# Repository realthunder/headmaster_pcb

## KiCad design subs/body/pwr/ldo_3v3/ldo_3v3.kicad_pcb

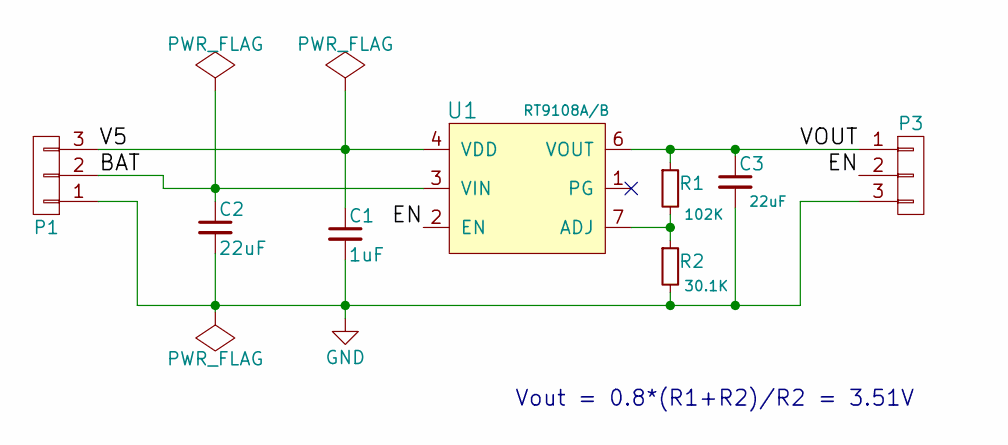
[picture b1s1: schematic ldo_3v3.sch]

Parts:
C1: 1uF; C_0402
C2, C3: 22uF; C_0805
P1, P3: CONN_01X01; Pin_Header_Straight_1x03
R1: 102K; R_0402
R2: 30.1K; R_0402
U1: RT9108A/B; SOIC-8-1EP_3.9x4.9mm_Pitch1.27mm

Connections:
/BAT: C2.1, P1.2, U1.3 (VIN)
/EN: P3.2, U1.2 (EN)
/V5: C1.1, P1.3, U1.4 (VDD)
/VOUT: C3.1, P3.1, R1.1, U1.6 (VOUT)
GND: C1.2, C2.2, C3.2, P1.1, P3.3, R2.2, U1.8 (GND), U1.9 (GND)
unnamed: R1.2, R2.1, U1.7 (ADJ)

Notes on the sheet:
Vout = 0.8*(R1+R2)/R2 = 3.51V

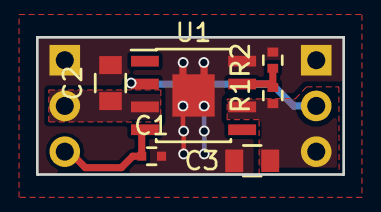
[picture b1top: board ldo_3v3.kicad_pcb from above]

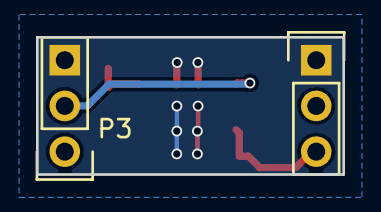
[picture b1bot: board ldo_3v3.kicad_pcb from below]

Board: 2 copper layers, 17.0 x 7.6 mm, 8 parts (2 on the bottom side), 6 nets.

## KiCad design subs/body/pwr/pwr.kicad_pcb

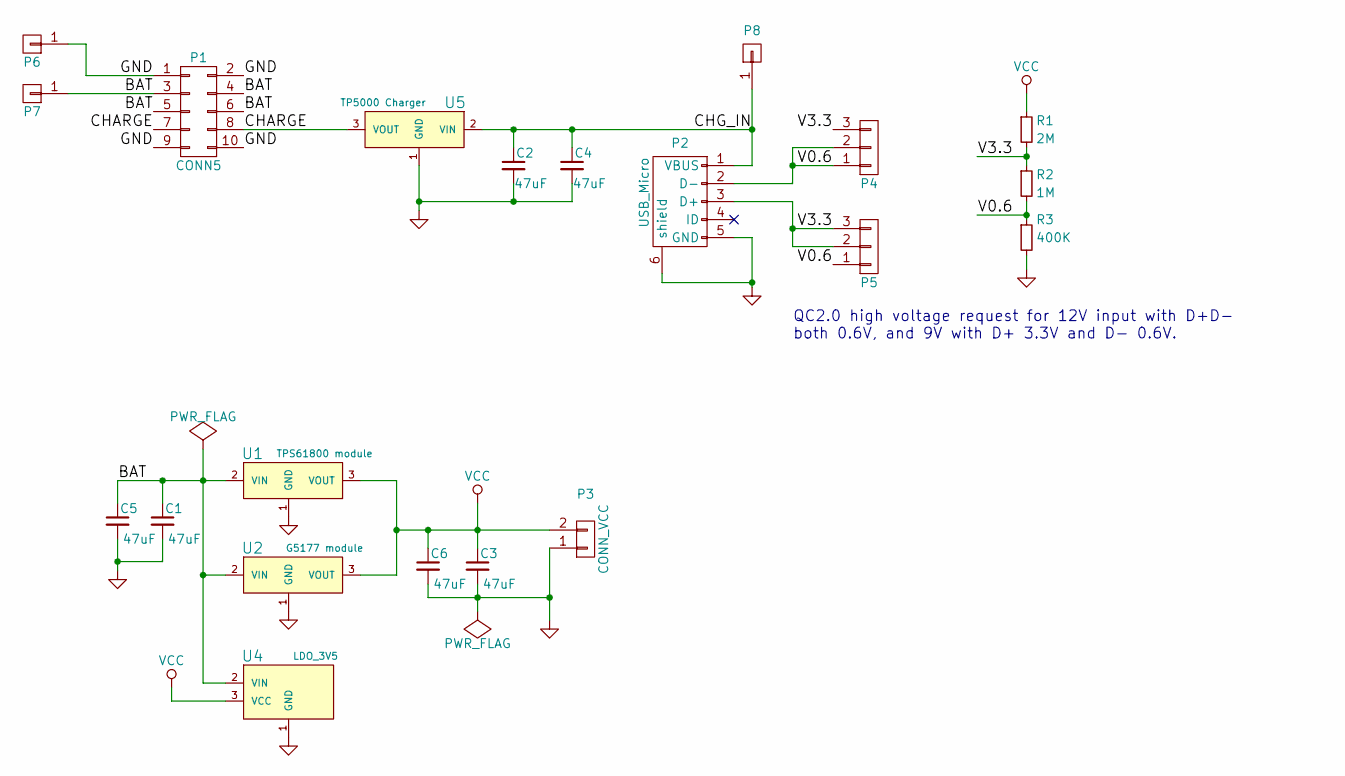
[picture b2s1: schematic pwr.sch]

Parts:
C1, C2, C3, C4, C5, C6: 47uF; C_1206
P1: CONN5; Socket_Strip_Straight_2x05
P2: USB_Micro; USB_Micro-B
P3: CONN_VCC; Socket_Strip_Straight_1x02
P4, P5: CONN_01X03; Pin_Header_Straight_1x03_Pitch1.27mm
P6, P7, P8: CONN_01X01; Pin_Header_Straight_1x01
R1: 2M; R_0402
R2: 1M; R_0402
R3: 400K; R_0402
U1: TPS61800 module; DCDC_Conv_TPS61800-Boost
U2: G5177 module; DCDC_Conv_G5177-Boost
U4: LDO_3V5; LDO_RT9018
U5: TP5000 Charger; DCDC_Charger-TP5000-Bucket

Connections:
/BAT: C1.1, C5.1, P1.3, P1.4, P1.5, P1.6, P7.1, U1.2 (VIN), U2.2 (VIN), U4.2 (VIN)
/CHARGE: P1.7, P1.8, U5.3 (VOUT)
/CHG_IN: C2.1, C4.1, P2.1 (VBUS), P8.1, U5.2 (VIN)
/V0.6: P2.2 (D-), P4.1, P4.2, P5.1, R2.2, R3.1
/V3.3: P2.3 (D+), P4.3, P5.2, P5.3, R1.2, R2.1
GND: C1.2, C2.2, C3.2, C4.2, C5.2, C6.2, P1.1, P1.2, P1.9, P1.10, P2.5 (GND), P2.6 (shield), P3.1, P6.1, R3.2, U1.1 (GND), U2.1 (GND), U4.1 (GND), U5.1 (GND)
VCC: C3.1, C6.1, P3.2, R1.1, U1.3 (VOUT), U2.3 (VOUT), U4.3 (VCC)

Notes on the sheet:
QC2.0 high voltage request for 12V input with D+D- both 0.6V, and 9V with D+ 3.3V and D- 0.6V.

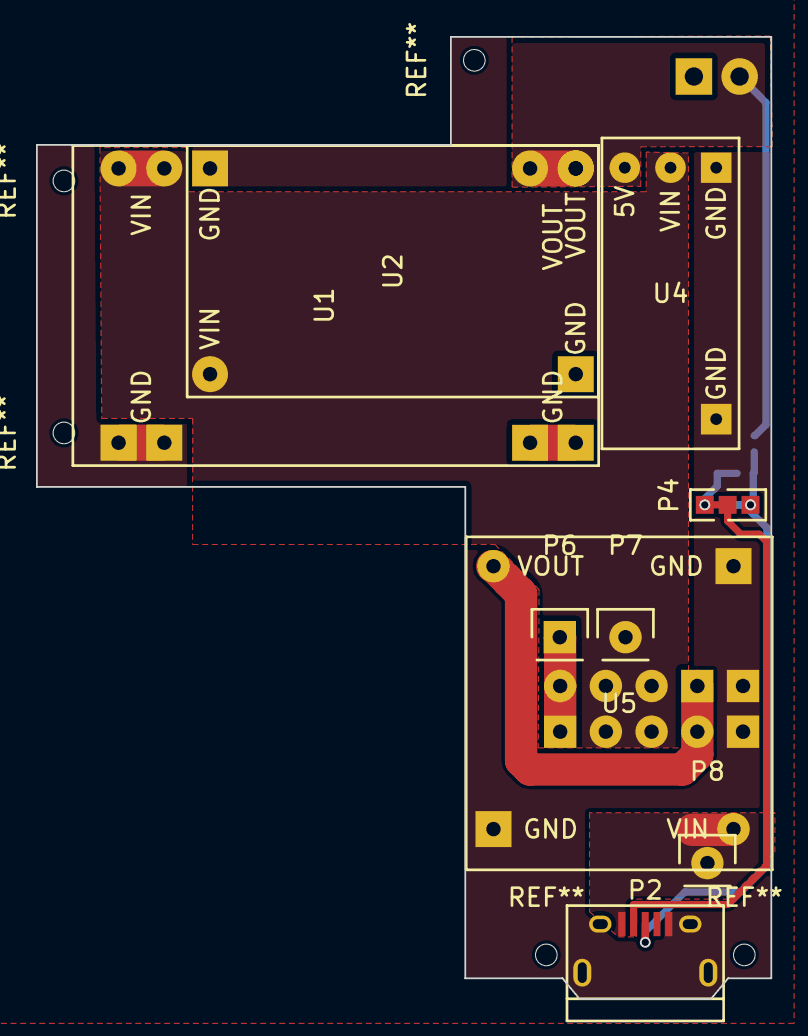
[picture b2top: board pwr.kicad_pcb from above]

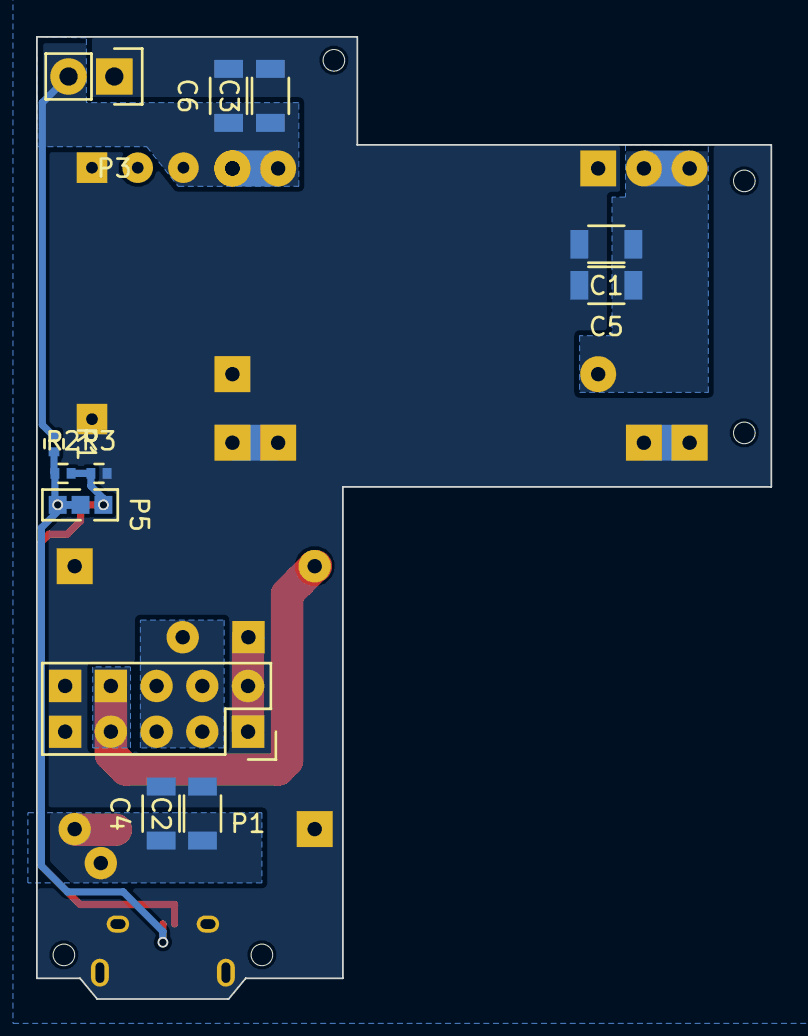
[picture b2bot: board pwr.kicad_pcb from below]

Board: 2 copper layers, 40.8 x 53.4 mm, 21 parts (12 on the bottom side), 7 nets.

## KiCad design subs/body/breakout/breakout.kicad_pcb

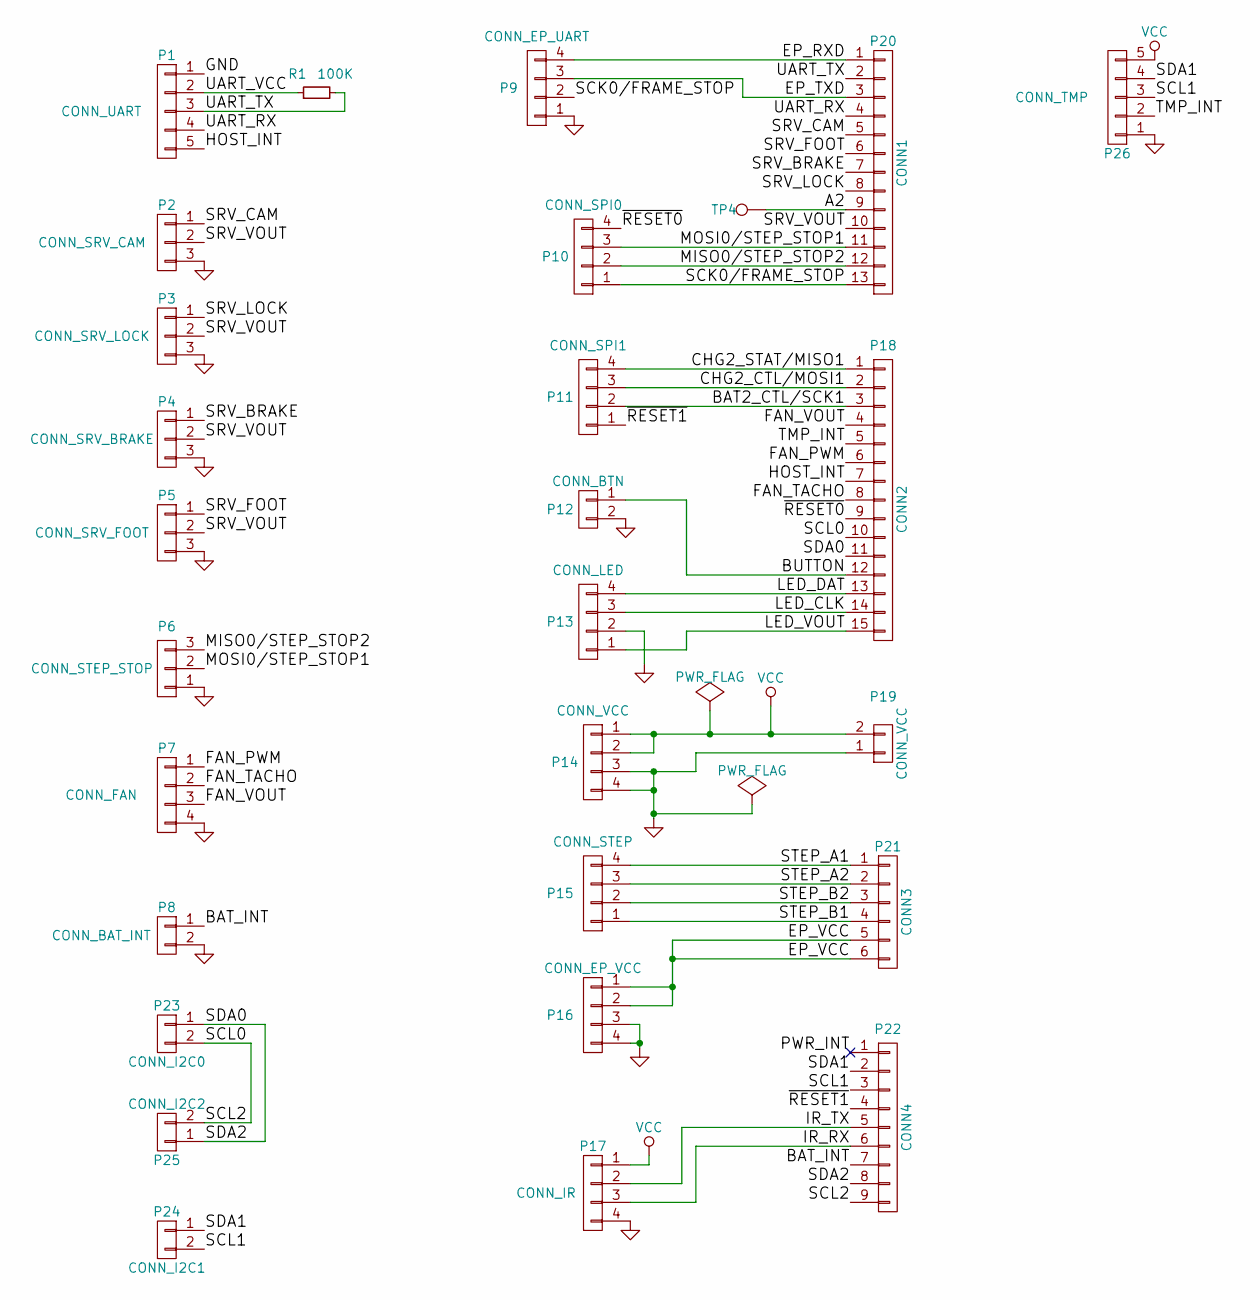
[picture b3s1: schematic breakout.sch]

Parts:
P1: CONN_UART; Molex_PicoBlade_53047-0510_DoubleSide
P2: CONN_SRV_CAM; Molex_PicoBlade_53047-0310_DoubleSide
P3: CONN_SRV_LOCK; Molex_PicoBlade_53047-0310_DoubleSide
P4: CONN_SRV_BRAKE; Molex_PicoBlade_53047-0310_DoubleSide
P5: CONN_SRV_FOOT; Molex_PicoBlade_53047-0310_DoubleSide
P6: CONN_STEP_STOP; Molex_PicoBlade_53047-0310_DoubleSide
P7: CONN_FAN; Molex_PicoBlade_53047-0410_DoubleSide
P8: CONN_BAT_INT; Molex_PicoBlade_53047-0210_DoubleSide
P9: CONN_EP_UART; Molex_PicoBlade_53047-0410_DoubleSide
P10: CONN_SPI0; Pin_Header_Straight_1x04_Pitch1.27mm
P11: CONN_SPI1; Pin_Header_Straight_1x04_Pitch1.27mm
P12: CONN_BTN; Molex_PicoBlade_53047-0210_DoubleSide
P13: CONN_LED; Molex_PicoBlade_53047-0410_DoubleSide
P14: CONN_VCC; Molex_PicoBlade_53047-0410_DoubleSide
P15: CONN_STEP; Molex_PicoBlade_53047-0410_DoubleSide
P16: CONN_EP_VCC; Molex_PicoBlade_53047-0410_DoubleSide
P17: CONN_IR; Molex_PicoBlade_53047-0410_DoubleSide
P18: CONN2; Socket_Strip_Straight_1x15_Pitch1.27mm
P19: CONN_VCC; Socket_Strip_Straight_1x02
P20: CONN1; Socket_Strip_Straight_1x13_Pitch1.27mm
P21: CONN3; Socket_Strip_Straight_1x06_Pitch1.27mm
P22: CONN4; Socket_Strip_Straight_1x09_Pitch1.27mm
P23: CONN_I2C0; Pin_Header_Straight_1x02_Pitch1.27mm
P24: CONN_I2C1; Molex_PicoBlade_53047-0210_DoubleSide
P25: CONN_I2C2; Pin_Header_Straight_1x02_Pitch1.27mm
P26: CONN_TMP; Molex_PicoBlade_53047-0510_DoubleSide
R1: 100K; R_0402
TP4: TEST_1P; Pin_Header_Straight_1x01_Pitch1.27mm

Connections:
/A2: P20.9, TP4.1
/BAT2_CTL/SCK1: P11.2, P18.3
/BAT_INT: P8.1, P22.7
/BUTTON: P12.1, P18.12
/CHG2_CTL/MOSI1: P11.3, P18.2
/CHG2_STAT/MISO1: P11.4, P18.1
/EP_RXD: P9.4, P20.1
/EP_TXD: P9.3, P20.3
/EP_VCC: P16.1, P16.2, P21.5, P21.6
/FAN_PWM: P7.1, P18.6
/FAN_TACHO: P7.2, P18.8
/FAN_VOUT: P7.3, P18.4
/HOST_INT: P1.5, P18.7
/IR_RX: P17.3, P22.6
/IR_TX: P17.2, P22.5
/LED_CLK: P13.3, P18.14
/LED_DAT: P13.4, P18.13
/LED_VOUT: P13.1, P18.15
/MISO0/STEP_STOP2: P6.3, P10.2, P20.12
/MOSI0/STEP_STOP1: P6.2, P10.3, P20.11
/SCK0/FRAME_STOP: P9.2, P10.1, P20.13
/SCL0: P18.10, P22.9, P23.2, P25.2
/SCL1: P22.3, P24.2, P26.3
/SDA0: P18.11, P22.8, P23.1, P25.1
/SDA1: P22.2, P24.1, P26.4
/SRV_BRAKE: P4.1, P20.7
/SRV_CAM: P2.1, P20.5
/SRV_FOOT: P5.1, P20.6
/SRV_LOCK: P3.1, P20.8
/SRV_VOUT: P2.2, P3.2, P4.2, P5.2, P20.10
/STEP_A1: P15.4, P21.1
/STEP_A2: P15.3, P21.2
/STEP_B1: P15.1, P21.4
/STEP_B2: P15.2, P21.3
/TMP_INT: P18.5, P26.2
/UART_RX: P1.4, P20.4
/UART_TX: P1.3, P20.2, R1.2
/UART_VCC: P1.2, R1.1
/~RESET0: P10.4, P18.9
/~RESET1: P11.1, P22.4
GND: P1.1, P2.3, P3.3, P4.3, P5.3, P6.1, P7.4, P8.2, P9.1, P12.2, P13.2, P14.3, P14.4, P16.3, P16.4, P17.4, P19.1, P26.1
VCC: P14.1, P14.2, P17.1, P19.2, P26.5

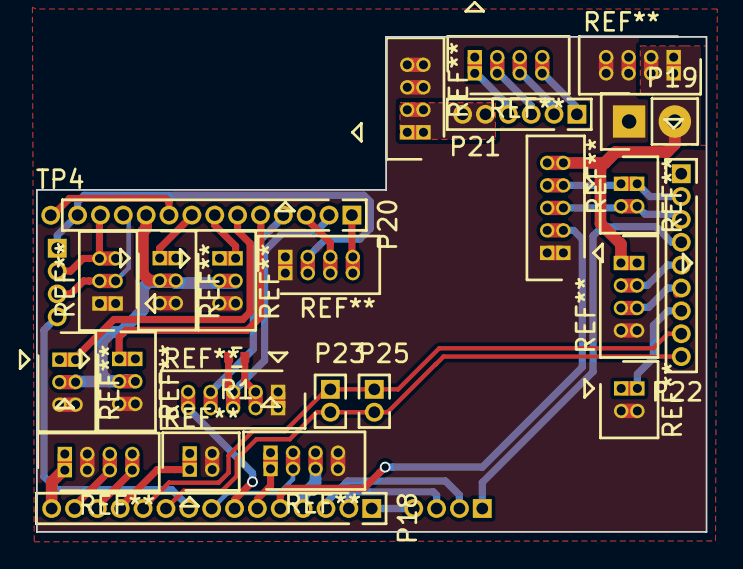
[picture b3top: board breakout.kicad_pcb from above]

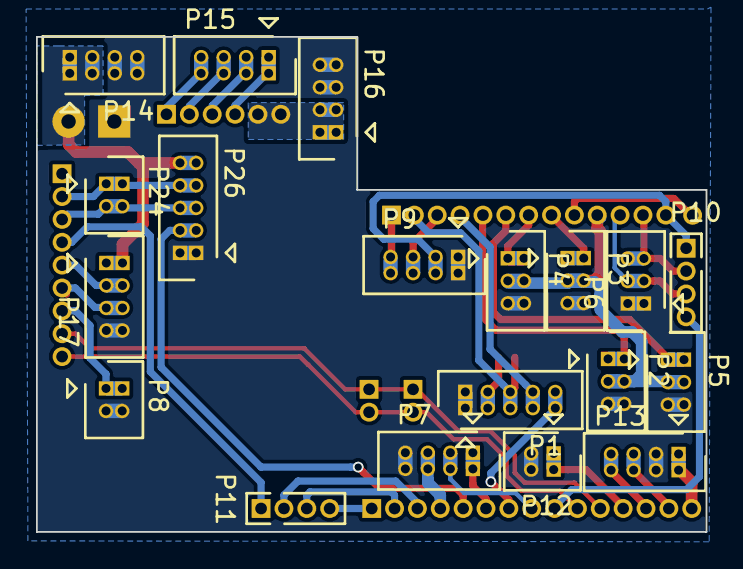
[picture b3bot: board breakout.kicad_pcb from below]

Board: 2 copper layers, 37.2 x 27.5 mm, 28 parts (19 on the bottom side), 42 nets.

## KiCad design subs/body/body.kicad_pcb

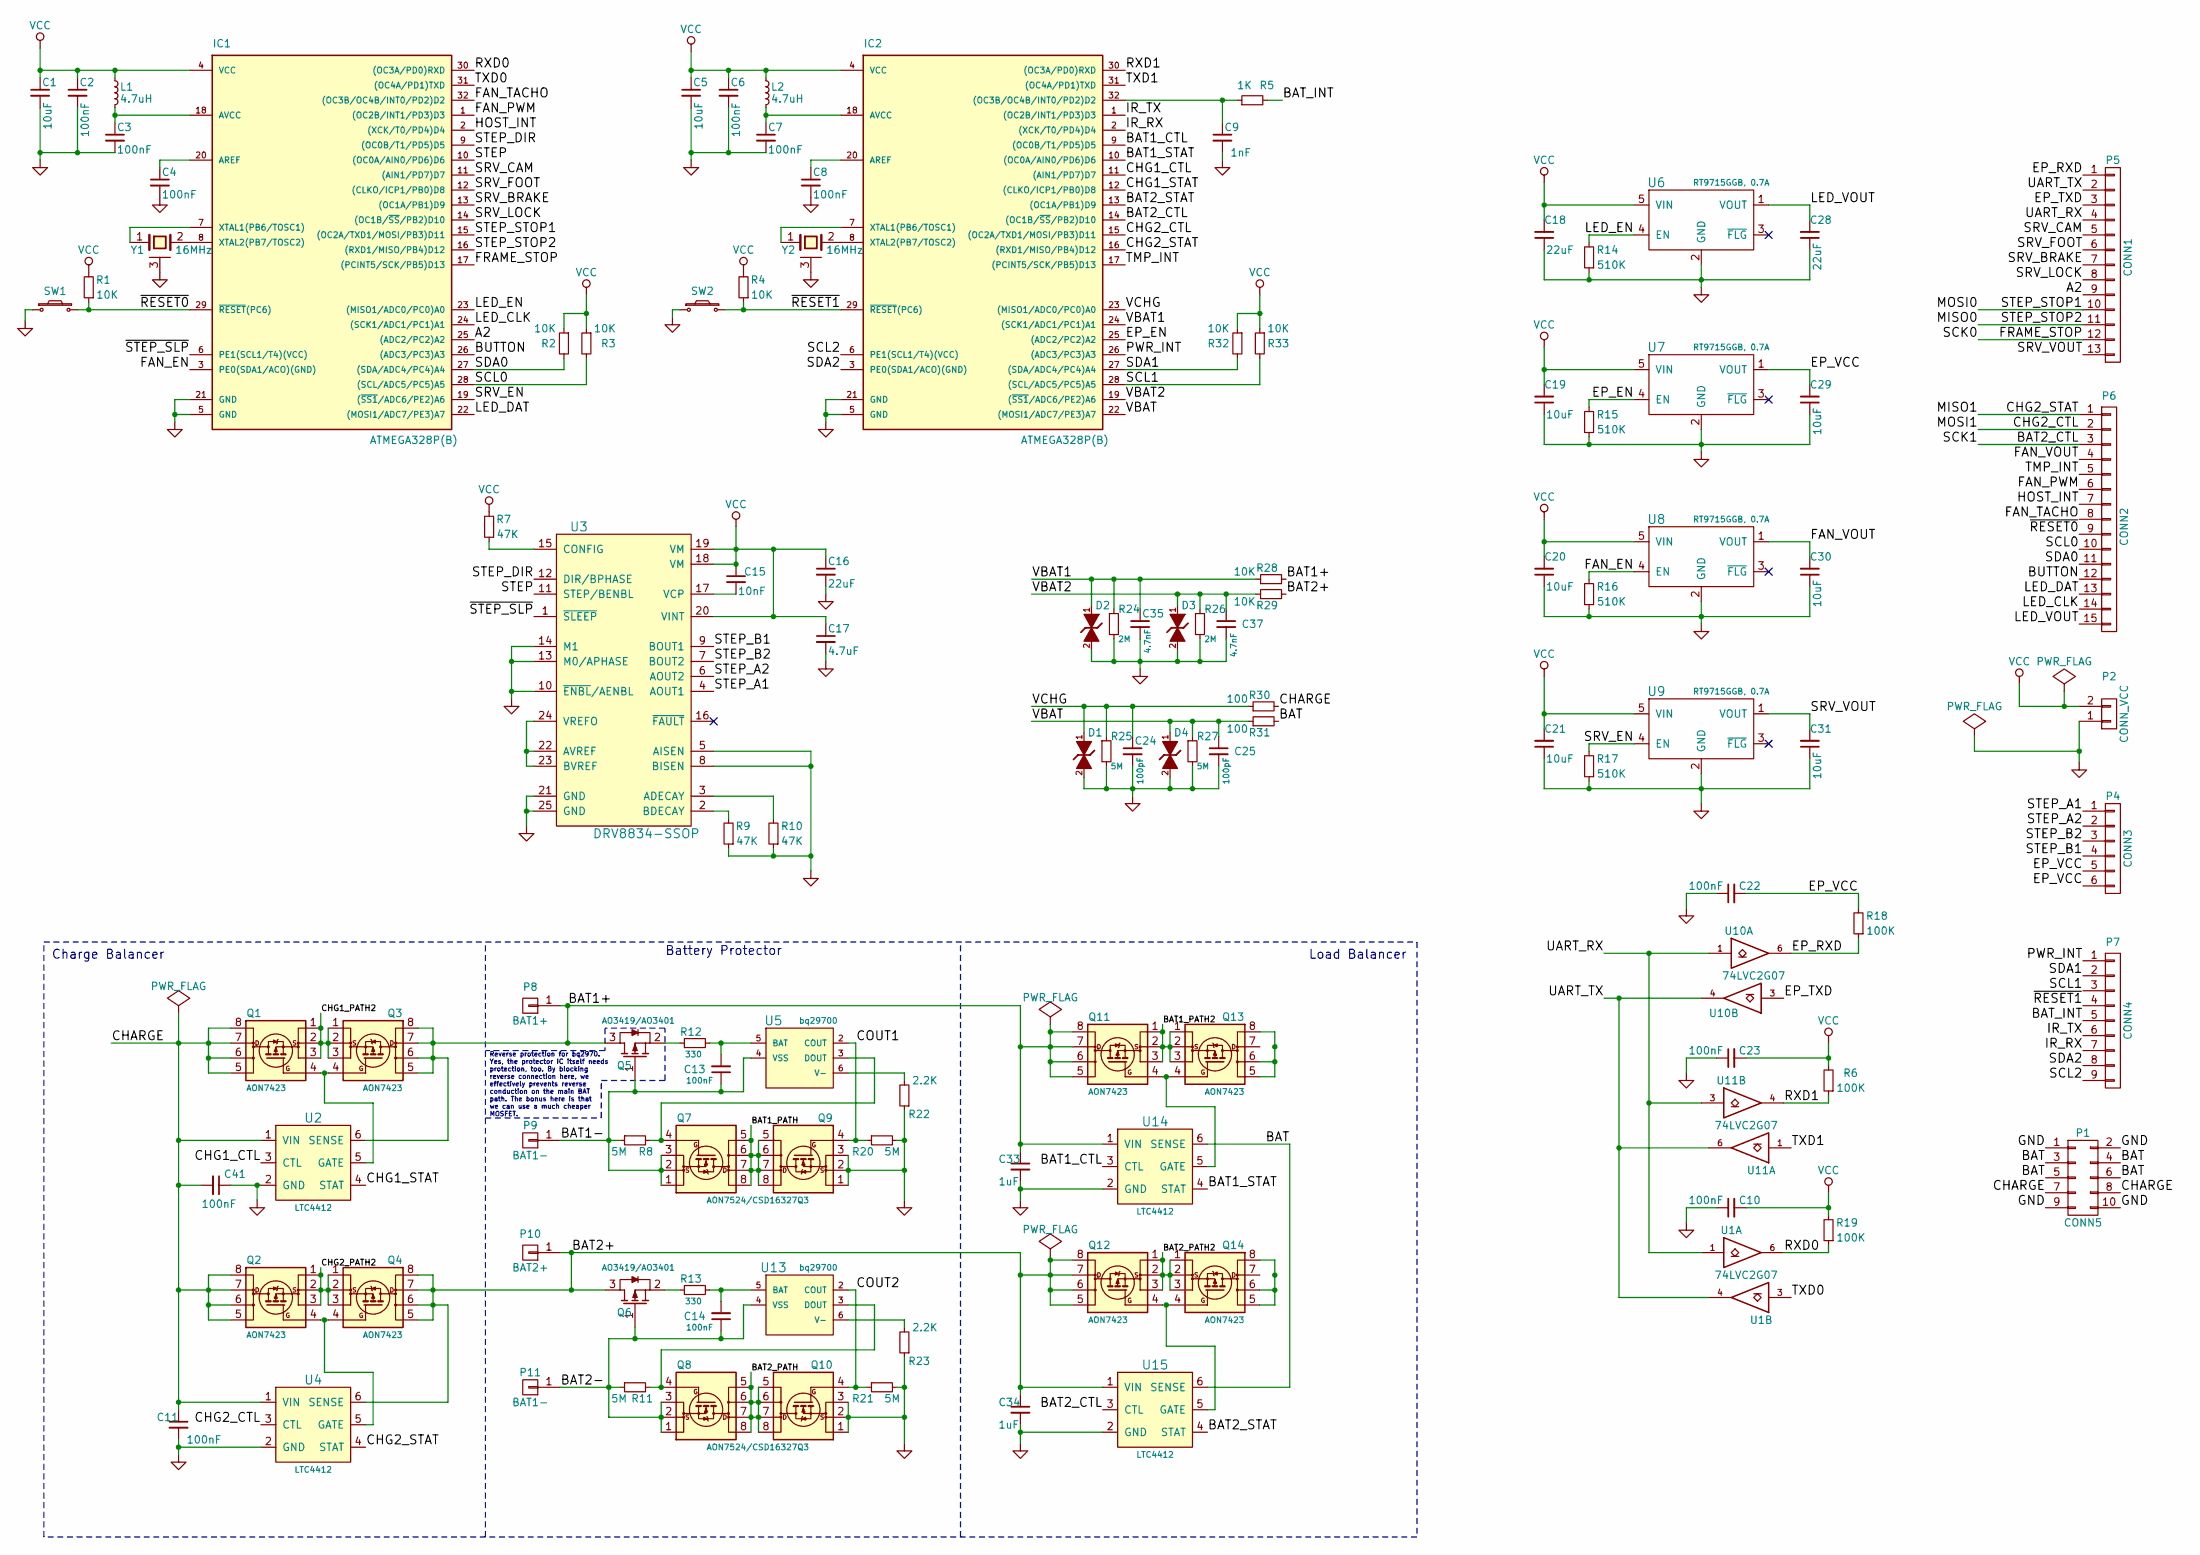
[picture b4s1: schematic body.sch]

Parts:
C1, C5, C19, C20, C21, C29, C30, C31: 10uF; C_0603
C2, C3, C4, C6, C7, C8, C10, C11, C13, C14, C22, C23, C41: 100nF; C_0402
C9: 1nF; C_0402
C15: 10nF; C_0402
C16, C18, C28: 22uF; C_0805
C17: 4.7uF; C_0603
C24, C25: 100pF; C_0402
C33, C34: 1uF; C_0402
C35, C37: 4.7nF; C_0402
D1, D2, D3, D4: ESB5B5.0S; SOD-523
IC1, IC2: ATMEGA328P(B); TQFP-32_7x7mm_Pitch0.8mm
L1, L2: 4.7uH; C_0603
P1: CONN5; Pin_Header_Straight_2x05
P2: CONN_VCC; Pin_Header_Straight_1x02
P4: CONN3; Pin_Header_Straight_1x06_Pitch1.27mm
P5: CONN1; Pin_Header_Straight_1x13_Pitch1.27mm
P6: CONN2; Pin_Header_Straight_1x15_Pitch1.27mm
P7: CONN4; Pin_Header_Straight_1x09_Pitch1.27mm
P8: BAT1+; Pin_Header_Straight_1x01
P9, P11: BAT1-; Pin_Header_Straight_1x01
P10: BAT2+; Pin_Header_Straight_1x01
Q1, Q2, Q3, Q4, Q11, Q12, Q13, Q14: AON7423; DFN-8-MOS_3x3mm_Pitch0.65mm
Q5, Q6: AO3419/AO3401; SOT-23
Q7, Q8: AON7524/CSD16327Q3; DFN-8-MOS_3x3mm_Pitch0.65mm
Q9, Q10: CSD16327Q3/AON7524; DFN-8-MOS_3x3mm_Pitch0.65mm
R1, R2, R3, R4, R28, R29, R32, R33: 10K; R_0402
R5: 1K; R_0402
R6, R18, R19: 100K; R_0402
R7, R9, R10: 47K; R_0402
R8, R11, R20, R21, R25, R27: 5M; R_0402
R12, R13: 330; R_0402
R14, R15, R16, R17: 510K; R_0402
R22, R23: 2.2K; R_0402
R24, R26: 2M; R_0402
R30, R31: 100; R_0402
SW1, SW2: SW_PUSH_Small_Horizontal; MTA2_4.5x2.3mm
U1, U10, U11: 74LVC2G07; SC-70-6
U2, U4, U14, U15: LTC4412; SOT-23-6
U3: DRV8834-SSOP; HTSSOP-24_4.4x7.8mm_Pitch0.65mm_1EP
U5, U13: bq29700; DFN-6-1.5x1.5mm_Pitch0.5mm
U6, U7, U8, U9: RT9715GGB, 0.7A; SOT-23-5
Y1, Y2: 16MHz; Resonator_3x1.3mm

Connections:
/A2: IC1.25 ((ADC2/PC2)A2), P5.9
/BAT1+: C33.1, P8.1, Q3.5 (D), Q3.6 (D), Q3.7 (D), Q3.8 (D), Q5.3 (D), Q11.5 (D), Q11.6 (D), Q11.7 (D), Q11.8 (D), R28.2, U2.6 (SENSE), U14.1 (VIN)
/BAT1-: C13.1, P9.1, Q5.1 (G), Q7.1 (S), Q7.2 (S), Q7.3 (S), R8.1, U5.4 (VSS)
/BAT1_CTL: IC2.9 ((OC0B/T1/PD5)D5), U14.3 (CTL)
/BAT1_PATH: Q7.5 (D), Q7.6 (D), Q7.7 (D), Q7.8 (D), Q9.5 (D), Q9.6 (D), Q9.7 (D), Q9.8 (D)
/BAT1_PATH2: Q11.1 (S), Q11.2 (S), Q11.3 (S), Q13.1 (S), Q13.2 (S), Q13.3 (S)
/BAT1_STAT: IC2.10 ((OC0A/AIN0/PD6)D6), U14.4 (STAT)
/BAT2+: C34.1, P10.1, Q4.5 (D), Q4.6 (D), Q4.7 (D), Q4.8 (D), Q6.3 (D), Q12.5 (D), Q12.6 (D), Q12.7 (D), Q12.8 (D), R29.2, U4.6 (SENSE), U15.1 (VIN)
/BAT2-: C14.1, P11.1, Q6.1 (G), Q8.1 (S), Q8.2 (S), Q8.3 (S), R11.1, U13.4 (VSS)
/BAT2_CTL: IC2.14 ((OC1B/~SS~/PB2)D10), P6.3, U15.3 (CTL)
/BAT2_PATH: Q8.5 (D), Q8.6 (D), Q8.7 (D), Q8.8 (D), Q10.5 (D), Q10.6 (D), Q10.7 (D), Q10.8 (D)
/BAT2_PATH2: Q12.1 (S), Q12.2 (S), Q12.3 (S), Q14.1 (S), Q14.2 (S), Q14.3 (S)
/BAT2_STAT: IC2.13 ((OC1A/PB1)D9), U15.4 (STAT)
/BAT_INT: P7.5, R5.2
/BUTTON: IC1.26 ((ADC3/PC3)A3), P6.12
/CHARGE: C11.1, C41.2, P1.7, P1.8, Q1.5 (D), Q1.6 (D), Q1.7 (D), Q1.8 (D), Q2.5 (D), Q2.6 (D), Q2.7 (D), Q2.8 (D), R30.2, U2.1 (VIN), U4.1 (VIN)
/CHG1_CTL: IC2.11 ((AIN1/PD7)D7), U2.3 (CTL)
/CHG1_PATH2: Q1.1 (S), Q1.2 (S), Q1.3 (S), Q3.1 (S), Q3.2 (S), Q3.3 (S)
/CHG1_STAT: IC2.12 ((CLKO/ICP1/PB0)D8), U2.4 (STAT)
/CHG2_CTL: IC2.15 ((OC2A/TXD1/MOSI/PB3)D11), P6.2, U4.3 (CTL)
/CHG2_PATH2: Q2.1 (S), Q2.2 (S), Q2.3 (S), Q4.1 (S), Q4.2 (S), Q4.3 (S)
/CHG2_STAT: IC2.16 ((RXD1/MISO/PB4)D12), P6.1, U4.4 (STAT)
/COUT1: Q9.4 (G), R20.1, U5.2 (COUT)
/COUT2: Q10.4 (G), R21.1, U13.2 (COUT)
/EP_EN: IC2.25 ((ADC2/PC2)A2), R15.2, U7.4 (EN)
/EP_RXD: P5.1, R18.1, U10.6
/EP_TXD: P5.3, U10.3
/FAN_EN: IC1.3 (PE0(SDA1/ACO)(GND)), R16.2, U8.4 (EN)
/FAN_PWM: IC1.1 ((OC2B/INT1/PD3)D3), P6.6
/FAN_TACHO: IC1.32 ((OC3B/OC4B/INT0/PD2)D2), P6.8
/FAN_VOUT: C30.2, P6.4, U8.1 (VOUT)
/FRAME_STOP: IC1.17 ((PCINT5/SCK/PB5)D13), P5.12
/HOST_INT: IC1.2 ((XCK/T0/PD4)D4), P6.7
/IR_RX: IC2.2 ((XCK/T0/PD4)D4), P7.7
/IR_TX: IC2.1 ((OC2B/INT1/PD3)D3), P7.6
/LED_CLK: IC1.24 ((SCK1/ADC1/PC1)A1), P6.14
/LED_DAT: IC1.22 ((MOSI1/ADC7/PE3)A7), P6.13
/LED_EN: IC1.23 ((MISO1/ADC0/PC0)A0), R14.2, U6.4 (EN)
/LED_VOUT: C28.2, P6.15, U6.1 (VOUT)
/MISO0: IC1.16 ((RXD1/MISO/PB4)D12), P5.11
/MOSI0: IC1.15 ((OC2A/TXD1/MOSI/PB3)D11), P5.10
/PWR_INT: IC2.26 ((ADC3/PC3)A3), P7.1
/RXD0: IC1.30 ((OC3A/PD0)RXD), R19.1, U1.6
/RXD1: IC2.30 ((OC3A/PD0)RXD), R6.1, U11.4
/SCL0: IC1.28 ((SCL/ADC5/PC5)A5), P6.10, R3.2
/SCL1: IC2.28 ((SCL/ADC5/PC5)A5), P7.3, R33.2
/SCL2: IC2.6 (PE1(SCL1/T4)(VCC)), P7.9
/SDA0: IC1.27 ((SDA/ADC4/PC4)A4), P6.11, R2.2
/SDA1: IC2.27 ((SDA/ADC4/PC4)A4), P7.2, R32.2
/SDA2: IC2.3 (PE0(SDA1/ACO)(GND)), P7.8
/SRV_BRAKE: IC1.13 ((OC1A/PB1)D9), P5.7
/SRV_CAM: IC1.11 ((AIN1/PD7)D7), P5.5
/SRV_EN: IC1.19 ((~SS1~/ADC6/PE2)A6), R17.2, U9.4 (EN)
/SRV_FOOT: IC1.12 ((CLKO/ICP1/PB0)D8), P5.6
/SRV_LOCK: IC1.14 ((OC1B/~SS~/PB2)D10), P5.8
/SRV_VOUT: C31.2, P5.13, U9.1 (VOUT)
/STEP: IC1.10 ((OC0A/AIN0/PD6)D6), U3.11 (STEP/BENBL)
/STEP_A1: P4.1, U3.4 (AOUT1)
/STEP_A2: P4.2, U3.6 (AOUT2)
/STEP_B1: P4.4, U3.9 (BOUT1)
/STEP_B2: P4.3, U3.7 (BOUT2)
/STEP_DIR: IC1.9 ((OC0B/T1/PD5)D5), U3.12 (DIR/BPHASE)
/TMP_INT: IC2.17 ((PCINT5/SCK/PB5)D13), P6.5
/TXD0: IC1.31 ((OC4A/PD1)TXD), U1.3
/TXD1: IC2.31 ((OC4A/PD1)TXD), U11.1
/UART_RX: P5.4, U1.1, U10.1, U11.3
/UART_TX: P5.2, U1.4, U10.4, U11.6
/VBAT: C25.1, D4.1, IC2.22 ((MOSI1/ADC7/PE3)A7), R27.1, R31.1
/VBAT1: C35.1, D2.1, IC2.24 ((SCK1/ADC1/PC1)A1), R24.1, R28.1
/VBAT2: C37.1, D3.1, IC2.19 ((~SS1~/ADC6/PE2)A6), R26.1, R29.1
/VCHG: C24.1, D1.1, IC2.23 ((MISO1/ADC0/PC0)A0), R25.1, R30.1
/~RESET0: IC1.29 (~RESET~(PC6)), P6.9, R1.1, SW1.2
/~RESET1: IC2.29 (~RESET~(PC6)), P7.4, R4.1, SW2.2
/~STEP_SLP: IC1.6 (PE1(SCL1/T4)(VCC)), U3.1 (~SLEEP)
EP_VCC: C22.2, C29.2, P4.5, P4.6, R18.2, U7.1 (VOUT), U10.5 (EP_VCC)
GND: C1.2, C2.2, C3.2, C4.2, C5.2, C6.2, C7.2, C8.2, C9.2, C10.1, C11.2, C16.2, C17.2, C18.1, C19.1, C20.1, C21.1, C22.1, C23.1, C24.2, C25.2, C28.1, C29.1, C30.1, C31.1, C33.2, C34.2, C35.2, C37.2, C41.1, D1.2, D2.2, D3.2, D4.2, IC1.5 (GND), IC1.21 (GND), IC2.5 (GND), IC2.21 (GND), P1.1, P1.2, P1.9, P1.10, P2.1, Q9.1 (S), Q9.2 (S), Q9.3 (S), Q10.1 (S), Q10.2 (S), Q10.3 (S), R9.1, R10.1, R14.1, R15.1, R16.1, R17.1, R20.2, R21.2, R22.1, R23.1, R24.2, R25.2, R26.2, R27.2, SW1.1, SW2.1, U1.2 (GND), U2.2 (GND), U3.5 (AISEN), U3.8 (BISEN), U3.10 (~ENBL~/AENBL), U3.13 (M0/APHASE), U3.14 (M1), U3.21 (GND), U3.25 (GND), U4.2 (GND), U6.2 (GND), U7.2 (GND), U8.2 (GND), U9.2 (GND), U10.2 (GND), U11.2 (GND), U14.2 (GND), U15.2 (GND), Y1.3 (case), Y2.3 (case)
unnamed: C3.1, IC1.18 (AVCC), L1.2
unnamed: C4.1, IC1.20 (AREF)
unnamed: C7.1, IC2.18 (AVCC), L2.2
unnamed: C8.1, IC2.20 (AREF)
unnamed: C9.1, IC2.32 ((OC3B/OC4B/INT0/PD2)D2), R5.1
unnamed: C13.2, R12.2, U5.5 (BAT)
unnamed: C14.2, R13.2, U13.5 (BAT)
unnamed: C15.2, U3.17 (VCP)
unnamed: IC1.7 (XTAL1(PB6/TOSC1)), Y1.1
unnamed: IC1.8 (XTAL2(PB7/TOSC2)), Y1.2
unnamed: IC2.7 (XTAL1(PB6/TOSC1)), Y2.1
unnamed: IC2.8 (XTAL2(PB7/TOSC2)), Y2.2
unnamed: Q1.4 (G), Q3.4 (G), U2.5 (GATE)
unnamed: Q2.4 (G), Q4.4 (G), U4.5 (GATE)
unnamed: Q5.2 (S), R12.1
unnamed: Q6.2 (S), R13.1
unnamed: Q7.4 (G), R8.2, U5.3 (DOUT)
unnamed: Q8.4 (G), R11.2, U13.3 (DOUT)
unnamed: Q11.4 (G), Q13.4 (G), U14.5 (GATE)
unnamed: Q12.4 (G), Q14.4 (G), U15.5 (GATE)
unnamed: R7.1, U3.15 (CONFIG)
unnamed: R9.2, U3.2 (BDECAY)
unnamed: R10.2, U3.3 (ADECAY)
unnamed: R22.2, U5.6 (V-)
unnamed: R23.2, U13.6 (V-)
unnamed: U3.22 (AVREF), U3.23 (BVREF), U3.24 (VREFO)
VCC: C1.1, C2.1, C5.1, C6.1, C10.2, C15.1, C16.1, C17.1, C18.2, C19.2, C20.2, C21.2, C23.2, IC1.4 (VCC), IC2.4 (VCC), L1.1, L2.1, P2.2, R1.2, R2.1, R3.1, R4.2, R6.2, R7.2, R19.2, R32.1, R33.1, U1.5 (VCC), U3.18 (VM), U3.19 (VM), U3.20 (VINT), U6.5 (VIN), U7.5 (VIN), U8.5 (VIN), U9.5 (VIN), U11.5 (VCC)

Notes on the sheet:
Charge Balancer
Battery Protector
Load Balancer
Reverse protection for bq2970. Yes, the protector IC itself needs protection, too. By blocking reverse connection here, we effectively prevents reverse conduction on the main BAT path. The bonus here is that we can use a much cheaper MOSFET.

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
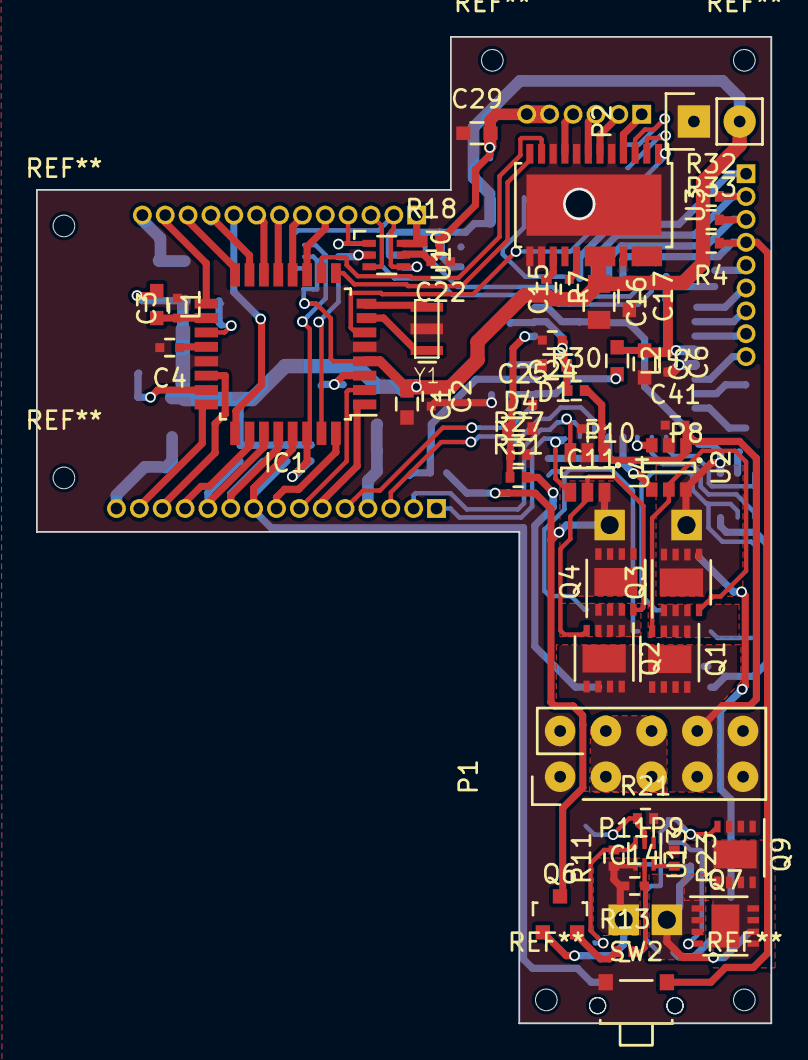
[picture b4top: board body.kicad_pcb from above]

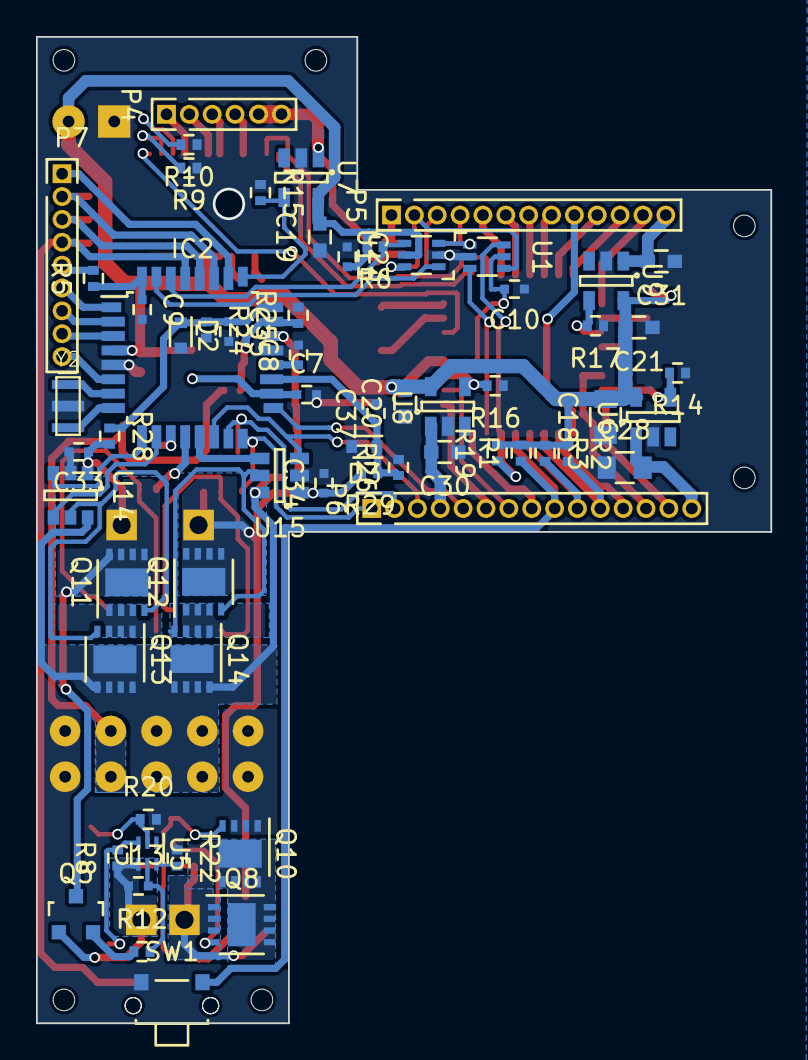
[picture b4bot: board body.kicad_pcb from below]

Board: 2 copper layers, 40.8 x 54.8 mm, 116 parts (63 on the bottom side), 104 nets.

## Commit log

2016-11-02 Init commit
2016-11-05 Before major layout change
2016-11-17 Finished routing of body board
2016-11-23 In progress, commit for backup
2016-11-26 Major modification of body board and companions
